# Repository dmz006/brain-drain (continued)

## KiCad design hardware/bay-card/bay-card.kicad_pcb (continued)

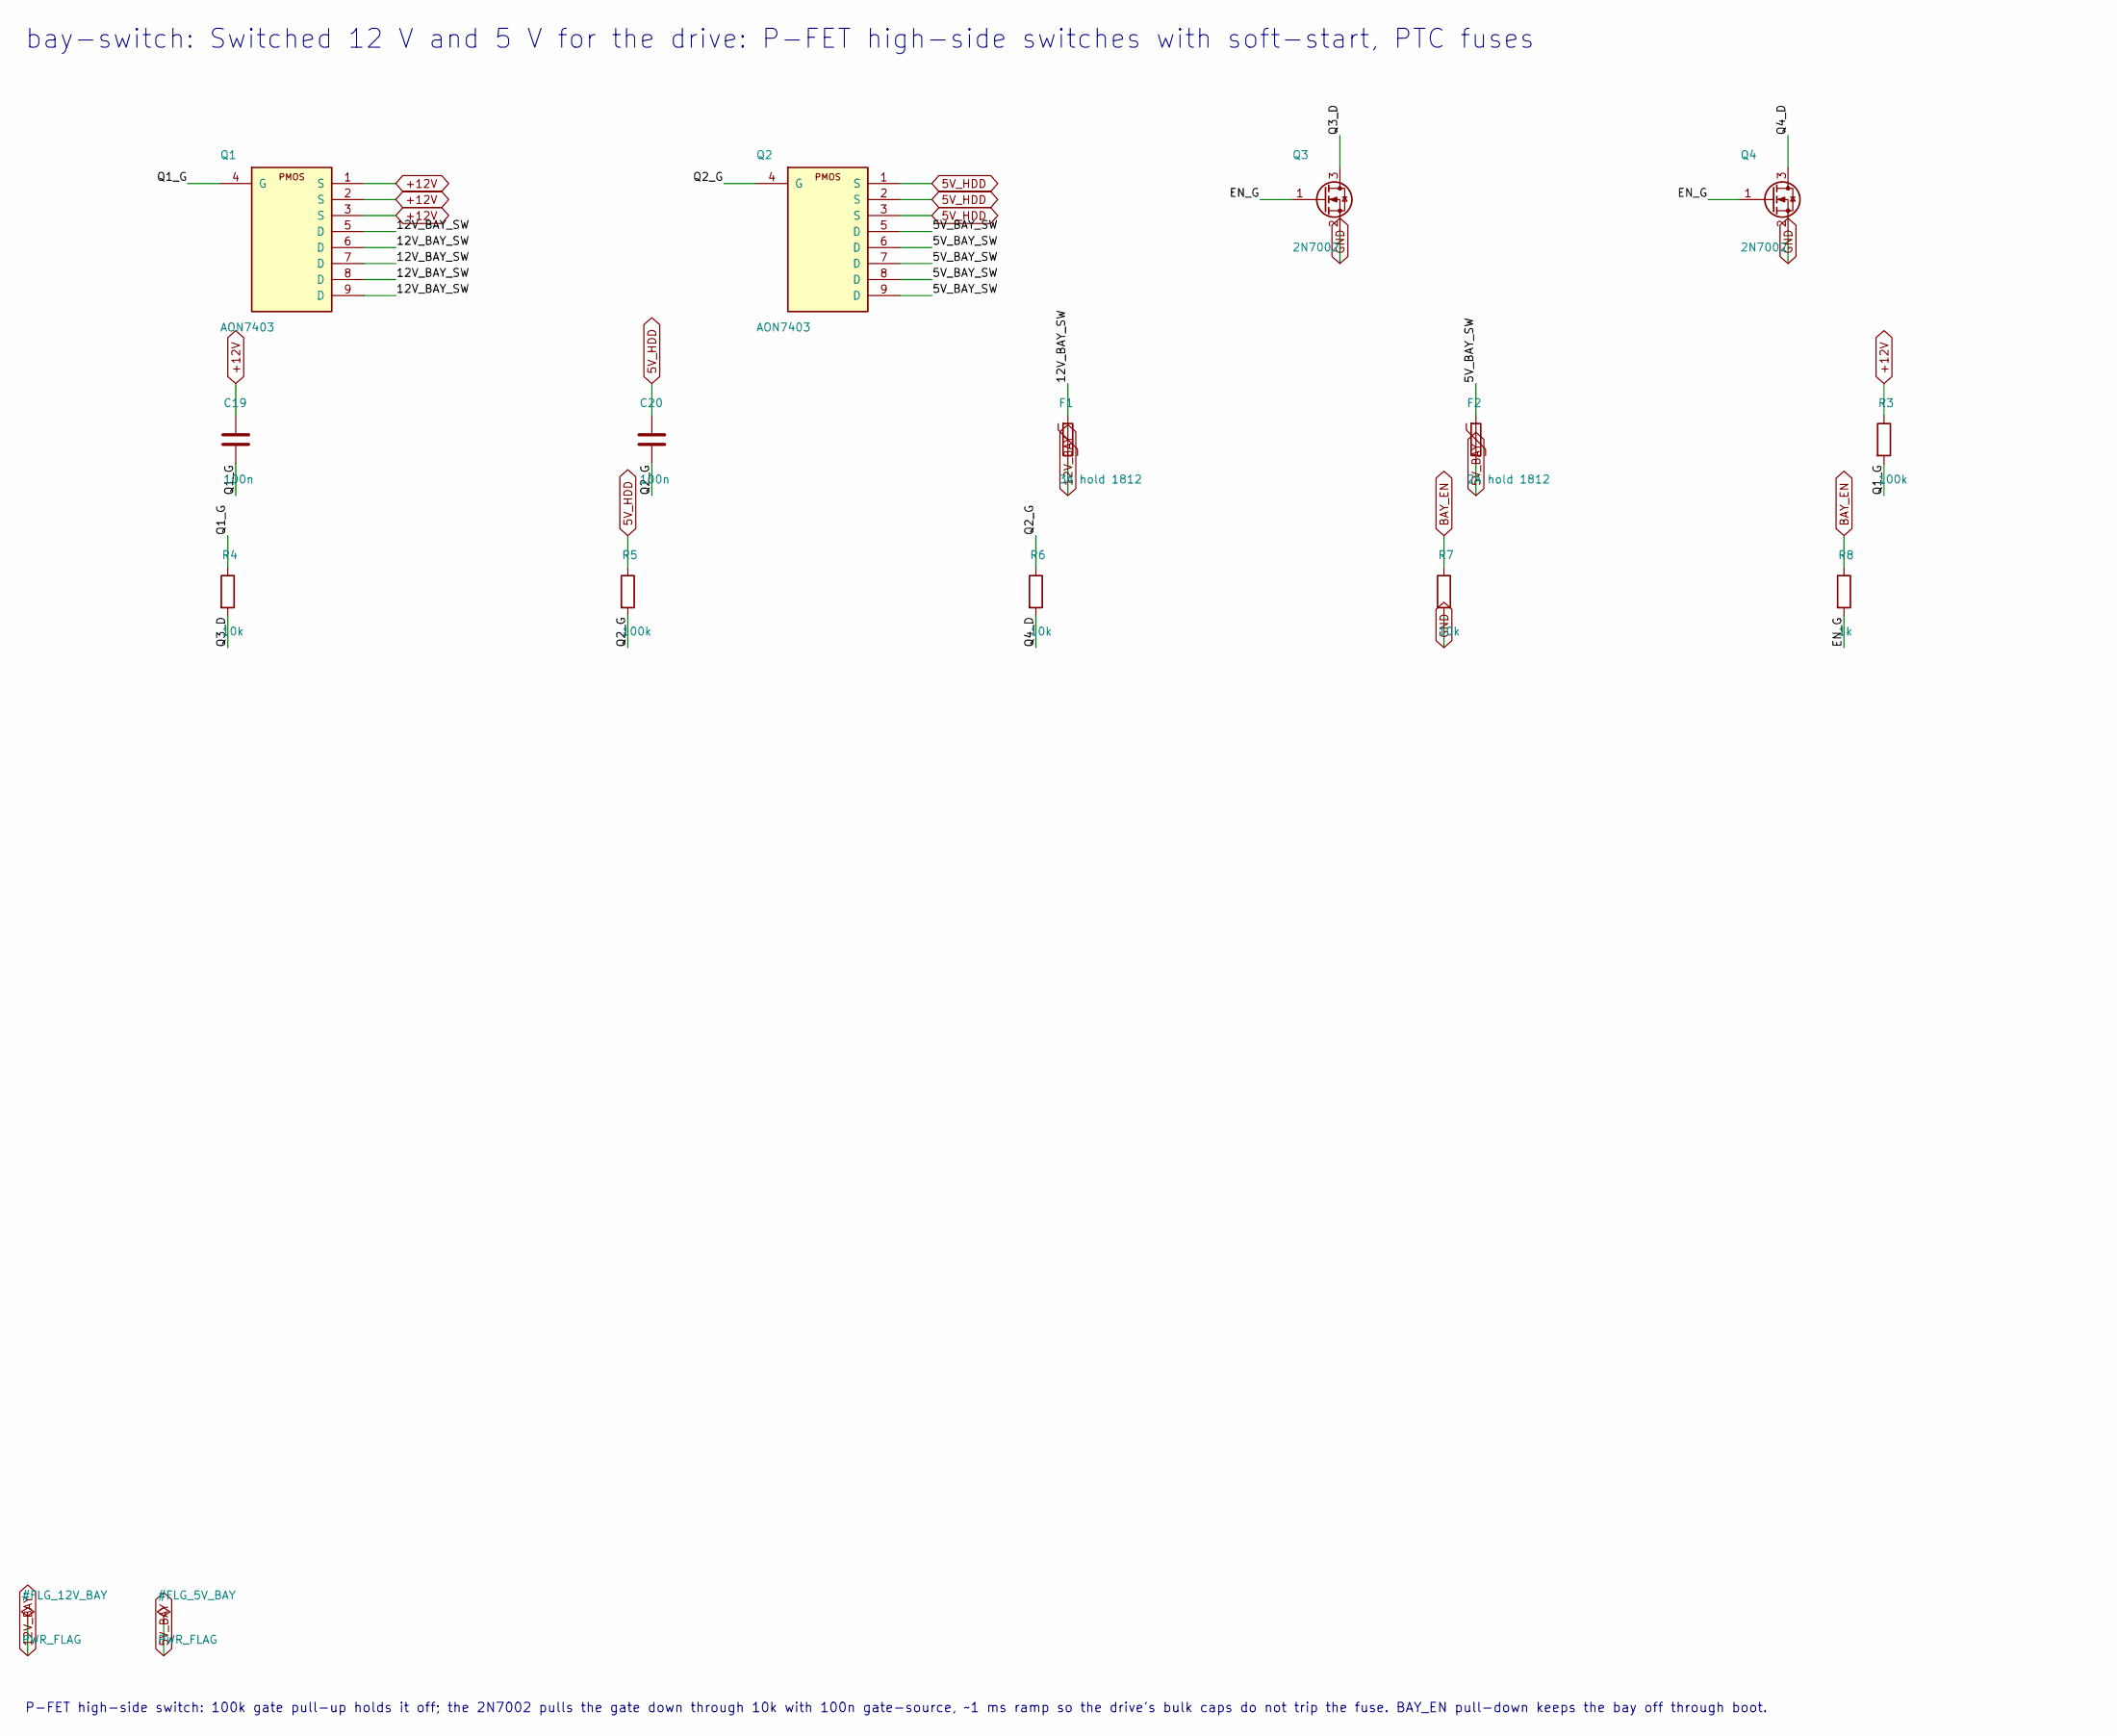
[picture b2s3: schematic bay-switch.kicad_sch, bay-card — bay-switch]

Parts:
C19, C20: 100n; C_0402_1005Metric
F1: 3A hold 1812; Fuse_1812_4532Metric
F2: 2A hold 1812; Fuse_1812_4532Metric
Q1, Q2: AON7403; DFN-8-1EP_3x3mm_P0.65mm_EP1.5x2.25mm
Q3, Q4: 2N7002; SOT-23
R3, R5: 100k; R_0402_1005Metric
R4, R6, R7: 10k; R_0402_1005Metric
R8: 1k; R_0402_1005Metric

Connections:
5V_BAY: F2.2; also elsewhere on the board
5V_BAY_SW: F2.1, Q2.5 (D), Q2.6 (D), Q2.7 (D), Q2.8 (D), Q2.9 (D)
5V_HDD: C20.1, Q2.1 (S), Q2.2 (S), Q2.3 (S), R5.1; also elsewhere on the board
12V_BAY: F1.2; also elsewhere on the board
12V_BAY_SW: F1.1, Q1.5 (D), Q1.6 (D), Q1.7 (D), Q1.8 (D), Q1.9 (D)
+12V: C19.1, Q1.1 (S), Q1.2 (S), Q1.3 (S), R3.1; also elsewhere on the board
BAY_EN: R7.1, R8.1; also elsewhere on the board
EN_G: Q3.1 (G), Q4.1 (G), R8.2
GND: Q3.2 (S), Q4.2 (S), R7.2; also elsewhere on the board
Q1_G: C19.2, Q1.4 (G), R3.2, R4.1
Q2_G: C20.2, Q2.4 (G), R5.2, R6.1
Q3_D: Q3.3 (D), R4.2
Q4_D: Q4.3 (D), R6.2

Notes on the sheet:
bay-switch: Switched 12 V and 5 V for the drive: P-FET high-side switches with soft-start, PTC fuses
P-FET high-side switch: 100k gate pull-up holds it off; the 2N7002 pulls the gate down through 10k with 100n gate-source, ~1 ms ramp so the drive's bulk caps do not trip the fuse. BAY_EN pull-down keeps the bay off through boot.

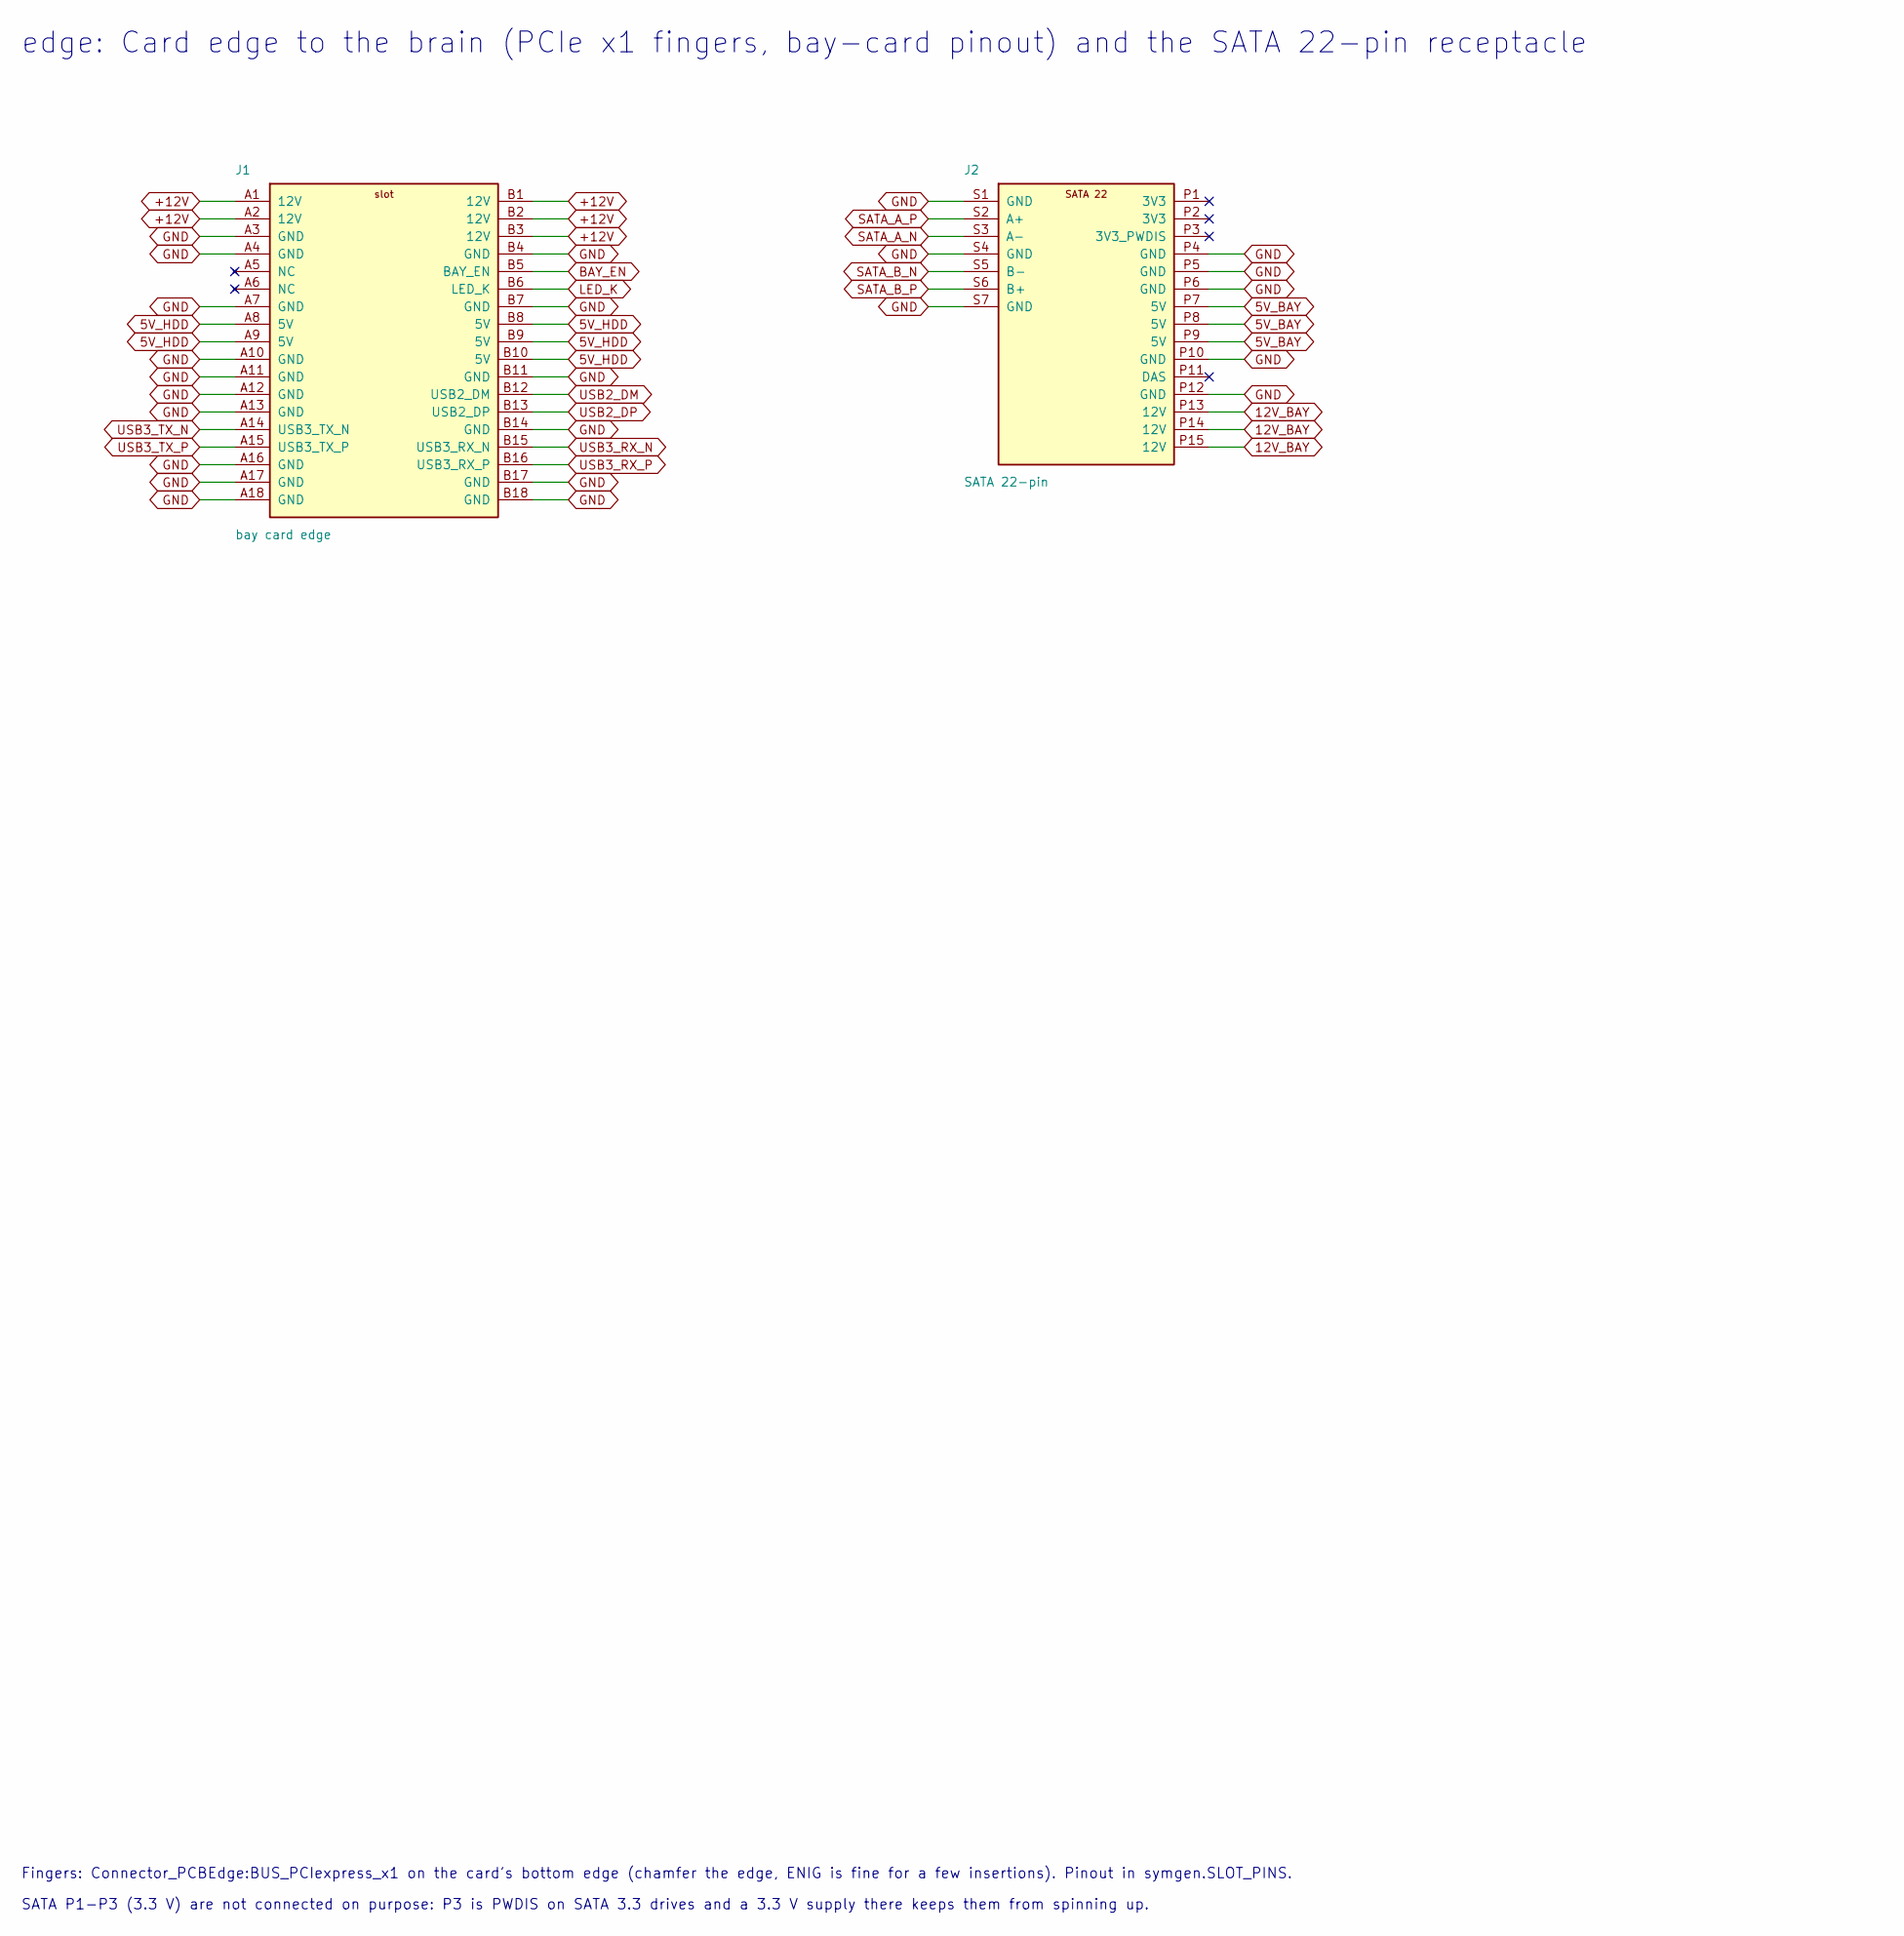
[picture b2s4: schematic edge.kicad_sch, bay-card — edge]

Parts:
J1: bay card edge; BUS_PCIexpress_x1
J2: SATA 22-pin; SATA_22pin_Receptacle_RA

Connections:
5V_BAY: J2.P7 (5V), J2.P8 (5V), J2.P9 (5V); also elsewhere on the board
5V_HDD: J1.A8 (5V), J1.A9 (5V), J1.B8 (5V), J1.B9 (5V), J1.B10 (5V); also elsewhere on the board
12V_BAY: J2.P13 (12V), J2.P14 (12V), J2.P15 (12V); also elsewhere on the board
+12V: J1.A1 (12V), J1.A2 (12V), J1.B1 (12V), J1.B2 (12V), J1.B3 (12V); also elsewhere on the board
BAY_EN: J1.B5 (BAY_EN); also elsewhere on the board
GND: J1.A3 (GND), J1.A4 (GND), J1.A7 (GND), J1.A10 (GND), J1.A11 (GND), J1.A12 (GND), J1.A13 (GND), J1.A16 (GND), J1.A17 (GND), J1.A18 (GND), J1.B4 (GND), J1.B7 (GND), J1.B11 (GND), J1.B14 (GND), J1.B17 (GND), J1.B18 (GND), J2.P4 (GND), J2.P5 (GND), J2.P6 (GND), J2.P10 (GND), J2.P12 (GND), J2.S1 (GND), J2.S4 (GND), J2.S7 (GND); also elsewhere on the board
LED_K: J1.B6 (LED_K); also elsewhere on the board
SATA_A_N: J2.S3 (A-); also elsewhere on the board
SATA_A_P: J2.S2 (A+); also elsewhere on the board
SATA_B_N: J2.S5 (B-); also elsewhere on the board
SATA_B_P: J2.S6 (B+); also elsewhere on the board
USB2_DM: J1.B12 (USB2_DM); also elsewhere on the board
USB2_DP: J1.B13 (USB2_DP); also elsewhere on the board
USB3_RX_N: J1.B15 (USB3_RX_N); also elsewhere on the board
USB3_RX_P: J1.B16 (USB3_RX_P); also elsewhere on the board
USB3_TX_N: J1.A14 (USB3_TX_N); also elsewhere on the board
USB3_TX_P: J1.A15 (USB3_TX_P); also elsewhere on the board

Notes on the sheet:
edge: Card edge to the brain (PCIe x1 fingers, bay-card pinout) and the SATA 22-pin receptacle
Fingers: Connector_PCBEdge:BUS_PCIexpress_x1 on the card's bottom edge (chamfer the edge, ENIG is fine for a few insertions). Pinout in symgen.SLOT_PINS.
SATA P1-P3 (3.3 V) are not connected on purpose: P3 is PWDIS on SATA 3.3 drives and a 3.3 V supply there keeps them from spinning up.

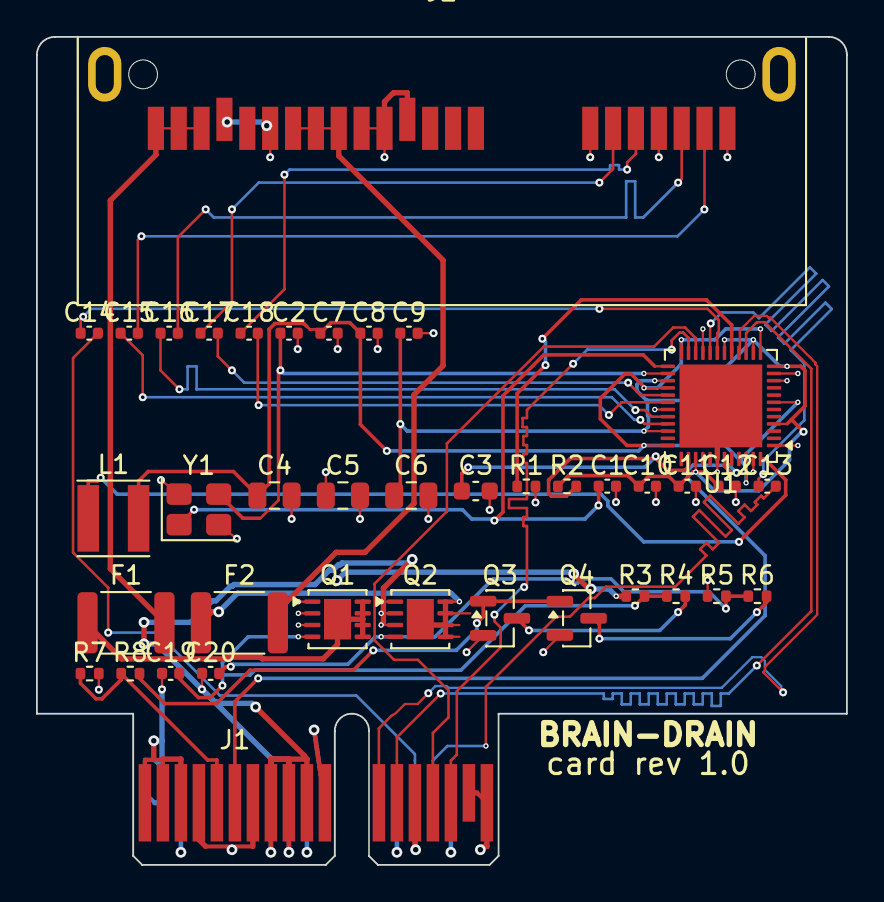
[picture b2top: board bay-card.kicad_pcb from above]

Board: 4 copper layers, 45.0 x 46.0 mm, 39 parts (0 on the bottom side), 37 nets.

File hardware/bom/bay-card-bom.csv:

refs,qty,value,footprint,manufacturer,mpn,description,usd_each,usd_total,status
"C1,C2",2,22p,C_0402_1005Metric,generic,,22 pF C0G 50 V 0402 (crystal load),0.01,0.02,
C3,1,2.2u,C_0603_1608Metric,generic,,2.2 uF X5R 10 V 0603,0.03,0.03,
"C4,C5,C6",3,10u 10V,C_0805_2012Metric,generic,,10 uF X5R 10 V 0805,0.05,0.15,
"C7,C8,C9,C10,C11,C12,C13,C14,C19,C20",10,100n,C_0402_1005Metric,generic,,"100 nF X7R 16 V or better, 0402",0.01,0.1,
"C15,C16,C17,C18",4,10n,C_0402_1005Metric,generic,,10 nF X7R 25 V 0402 (SATA AC coupling),0.01,0.04,
F1,1,3A hold 1812,Fuse_1812_4532Metric,generic,,"PTC resettable fuse 1812, 3 A hold (bay 12 V), 15 V or better",0.3,0.3,verify
F2,1,2A hold 1812,Fuse_1812_4532Metric,generic,,"PTC resettable fuse 1812, 2 A hold (bay 5 V), 6 V or better",0.3,0.3,verify
J1,1,bay card edge,BUS_PCIexpress_x1,(board),,"PCI Express x1 card-edge fingers on the card itself, ENIG, chamfered tab",0.0,0.0,
J2,1,SATA 22-pin,SATA_22pin_Receptacle_RA,Molex,47018-4001,"SATA 22-pin (7+15) host receptacle, top mount, PCB-edge type, tape and reel with cap",1.5,1.5,verify
L1,1,4.7u 1A,L_Taiyo-Yuden_NR-40xx,generic,,"4.7 uH, 1 A, 4 x 4 mm (ASM1153E internal core switcher)",0.3,0.3,verify
"Q1,Q2",2,AON7403,DFN-8-1EP_3x3mm_P0.65mm_EP1.5x2.25mm,Alpha & Omega,AON7403,"P-MOSFET -30 V, DFN 3x3-8: S 1-3, G 4, D 5-8 + EP (bay 12 V and 5 V switches)",0.8,1.6,
"Q3,Q4",2,2N7002,SOT-23,generic,,"N-MOSFET 60 V 2N7002, SOT-23 (gate driver)",0.05,0.1,
R1,1,12.1k 1%,R_0402_1005Metric,generic,,"resistor 1 %, thick film (value as listed)",0.005,0.005,
"R2,R4,R6,R7",4,10k,R_0402_1005Metric,generic,,"resistor 1 %, thick film (value as listed)",0.005,0.02,
"R3,R5",2,100k,R_0402_1005Metric,generic,,"resistor 1 %, thick film (value as listed)",0.005,0.01,
R8,1,1k,R_0402_1005Metric,generic,,"resistor 1 %, thick film (value as listed)",0.005,0.005,
U1,1,ASM1153E,QFN-48-1EP_6x6mm_P0.4mm_EP4.6x4.6mm,ASMedia,ASM1153E,"USB 3.0 to SATA 6G bridge, QFN-48 6 x 6, SAT passthrough",3.0,3.0,verify
Y1,1,30MHz CL=16pF,Crystal_SMD_3225-4Pin_3.2x2.5mm,generic,,"30 MHz crystal, 3.2 x 2.5 mm, CL 16 pF (bridge default clock strap)",0.3,0.3,

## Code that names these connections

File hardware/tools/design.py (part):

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    d.sheet("cm5", "Compute Module 5 (wireless): power, control, GPIO, microSD, USB-C, UART, RTC cell, fan, DIP, LEDs, OLED")
    d.sheet("usb3-hub-A", "USB5744 hub A on CM5 USB3-0, bay slots 1-4")
    d.sheet("usb3-hub-B", "USB5744 hub B on CM5 USB3-1, bay slots 5-8")
    d.sheet("bay-slots", "Eight bay slots (PCIe x1 sockets, bay-card pinout): USB 3, USB 2, 12 V, 5 V, BAY_EN, bay LEDs")
    d.sheet("m2-nvme", "Bay 9: M.2 M-key on PCIe Gen3 x1, 3V3_M2 buck + load switch, lid switch")

    # ---------------------------------------------------------------- power input
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    d.part("C2", "Device:C", "22u 10V", s, FP["C0805"])
    d.net("5V_SYS", "M1.5V", "C1.1", "C2.1")
    d.net("GND", "M1.GND", "C1.2", "C2.2")
    d.net("CM5_3V3", "M1.CM5_3.3V", "M1.GPIO_VREF")
    d.nc("M1.CM5_1.8V", "M1.PWR_Button", "M1.PMIC_Enable", "M1.LED_nPWR", "M1.EEPROM_nWP", "M1.WL_nDisable",
         "M1.BT_nDisable", "M1.SCL0", "M1.SDA0", "M1.CAM_GPIO0", "M1.CAM_GPIO1",
         "M1.SD_VDD_OVERRIDE", "M1.Ethernet_SYNC_OUT")
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    # UART debug
    d.part("J7", "Connector_Generic:Conn_01x03", "UART0 GND/TX/RX", s, FP["HDR1x3"])
    d.net("GND", "J7.1")
    d.net("UART0_TXD", "M1.GPIO14", "J7.2")
    d.net("UART0_RXD", "M1.GPIO15", "J7.3")
    # Fan header (Pi pinout: 1 GND, 2 +5V, 3 tacho, 4 PWM)
    d.part("J40", "Connector_Generic:Conn_01x04", "Fan GND/5V/TACH/PWM", s, FP["FAN4"])
    d.net("GND", "J40.1")
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    d.net("D2_A", "R2.2", "D2.A")
    d.net("LED_nACT", "D2.K", "M1.LED_nACT")
    d.net("D3_A", "R3.2", "D3.A")
    d.net("STATUS_LED", "D3.K", "M1.GPIO26")
    d.note(s, "LED_nACT is an open-drain 20 mA output on the CM5: it sinks D2 directly. GPIO26 sinks D3 (software drives it low to light).")
    # DIP switch: GPIO16,17,20,21,22,23,24,25 = DIP1..8, other side GND (internal pull-ups in software)
    d.part("SW1", "Switch:SW_DIP_x08", "DIP x8", s, FP["DIP8"])
    for i, g in enumerate((16, 17, 20, 21, 22, 23, 24, 25), start=1):
        d.net(f"DIP{i}", f"M1.GPIO{g}", f"SW1.{i}")
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    d.part("J41", "Connector_Generic:Conn_01x04", "OLED GND/VCC/SCL/SDA", s, FP["HDR1x4"])
    d.net("GND", "J41.1")
    d.net("+3V3", "J41.2")
    d.net("I2C1_SCL", "M1.GPIO3", "J41.3")
    d.net("I2C1_SDA", "M1.GPIO2", "J41.4")
    # microSD (CM5 Lite)
    d.part("J3", "Connector:Micro_SD_Card", "microSD", s, FP["MICROSD"])
    d.net("SD_CLK", "M1.SD_CLK", "J3.CLK")
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    d.note(s, "USB-C is a device port (rpiboot / gadget). As on the CM5IO, CC1/CC2 go straight to the CM5, which presents the sink pull-downs itself; VBUS is not connected (the board is powered from 12 V). USB_OTG_ID floats = device.")
    # bay enables and M.2 controls from GPIO
    for b, g in ((1, 5), (2, 6), (3, 12), (4, 13), (5, 7), (6, 8), (7, 9), (8, 10)):
        d.net(f"BAY_EN{b}", f"M1.GPIO{g}")
    d.net("M2_DOOR", "M1.GPIO4")
    d.net("M2_PWR_EN", "M1.GPIO27")
    d.net("M2_PEDET", "M1.GPIO19")
    d.nc("M1.ID_SD", "M1.ID_SC", "M1.GPIO11")
    # unused high-speed / video pins on M2 unit 2
    for p in kilib.get("brain-drain:CM5").pins:
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            d.nc(f"J50.{p.number}")
    d.note(s, "Polarity: CM5 TX_P -> PETp0 (49), TX_N -> PETn0 (47), PERp0 (43) -> RX_P, PERn0 (41) -> RX_N. The CM5IO reference wires both pairs inverted (TX_P to 47, RX_P to 41), which PCIe link training tolerates; either works.")
    d.note(s, "Only PCIe lane 0 is wired (x1). PET = host transmit (CM5 TX, AC caps on the module). PER = host receive: per the M.2 spec the SSD carries its own TX caps, so R502/R503 are 0R; the same 0402 pads take 100n if a module without caps turns up.")
    d.note(s, "PEDET (pin 69) is pulled up and read by GPIO19: an M.2 SATA module grounds it, and the software refuses the bay instead of trying PCIe.")
    d.note(s, "Door switch SW3 to GPIO4 (software pull-up): closed = low = door shut. Software powers the slot (M2_PWR_EN, GPIO27 -> U50) and rescans PCIe.")
    return d


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    d.net("5V_BAY", "J2.P7", "J2.P8", "J2.P9")
    d.net("12V_BAY", "J2.P13", "J2.P14", "J2.P15")
    d.nc("J2.P1", "J2.P2", "J2.P3", "J2.P11")
    d.net("LED_K", "U1.GPIO0")
    d.nc("U1.GPIO1", "U1.GPIO2", "U1.GPIO3", "U1.GPIO4", "U1.GPIO5", "U1.GPIO6", "U1.GPIO7",
         "U1.HDDPC", "U1.I2C_DATA", "U1.I2C_CLK", "U1.UART_RX", "U1.UART_TX")
    d.note(s, "ASM1153E runs from 5 V only (the brain's always-on 5V_HDD rail through the edge): VBUS_LDO -> VCCO (3.3 V) and VCCIN -> LXI switcher -> 1.05 V core.")
    d.note(s, "Clock straps GPIO3/GPIO7 at their internal pull-up default (11) = 30 MHz crystal. GPIO6 default = I2C mode, no SPI ROM. Bay activity LED assumed on GPIO0 (verify on the bench); it sinks the brain's LED through the edge.")

    # ---------------------------------------------------------------- bay power switch
    s = "bay-switch"
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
